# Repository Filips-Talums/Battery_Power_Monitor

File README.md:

# Supply_Power_Monitor

## Overview

Battery_Power_Monitor is an ESP32-based DC inline power monitor designed to measure voltage, current, and power while a DC source powers an external load.

The system is designed to support a wide range of DC input sources from 6 V to 12 V and aims to act as a compact monitoring tool for electronics development and testing.

---

## Project Goals

Through this project I aim to learn:

- PCB design using KiCad
- Circuit testing and calibration
- ESP32 microcontroller development
- Embedded systems programming using C++
- Professional project documentation using GitHub
- Power monitoring and sensor integration

---

## Components Used

- ESP32 Development Board
- INA226 Power Monitoring Sensor
- 128x64 I2C OLED Display
- 6 V buck-boost converter module for powering the ESP32 from a 6–12 V input
- Screw Terminals
- Electrolytic and Ceramic Capacitors
- Fuse Protection

---

## How It Works

An external DC power source between 6 V and 12 V is connected through screw terminals.

The input power is split into two sections:

- A regulated 6 V supply powers the ESP32 and OLED display
- The main power line passes through the INA226 current and voltage sensor before reaching the external load

The INA226 measures:

- Bus Voltage
- Current Draw
- Power Consumption

The ESP32 processes this data and displays the measured values on the OLED screen.

The device is intended to help monitor power usage, diagnose faults, and test small electronics projects safely.

---

## System Diagram

### Power Flow

```text
DC Input (6 V - 12 V)
        │
        ├──→ LM2596S Buck Converter (5 V)
        │          │
        │          └──→ ESP32 ──→ OLED Display
        │                        └──→ Buzzer Warning
        │                        └──→ LED Warning
        └──→ Fuse Protection
                   │
                   └──→ INA226 Power Monitor
                                │
                                └──→ Load Output
```
## Current Status

The breadboard prototype is now working. The ESP32 successfully reads bus voltage and shunt voltage from the INA226 power monitoring sensor and displays voltage, current, and power on the OLED display.

Initial voltage calibration has been completed using a multimeter. The raw INA226 bus voltage reading was found to be consistently higher than the multimeter reading, so a software correction factor was applied.

Current calculation has been implemented using the INA226 shunt voltage and the R100 0.1 Ω shunt resistor. Initial current testing has been carried out using resistor loads and a multimeter. The monitor initially under-read current slightly, so a current correction factor was added in software. Further load testing with higher-current loads is still planned.

* Project requirements defined
* Main components selected
* System block diagram completed
* PlatformIO project created
* INA226 integrated with the ESP32
* OLED display integrated and tested
* Live voltage, current and power measurements displayed
* Voltage readings calibrated against a multimeter
* Current readings tested and calibrated using multiple resistive loads
* Breadboard prototype completed and tested
* Circuit transferred from breadboard to perfboard
* LM2596 buck converter configured to provide a regulated 5 V supply
* Schottky diode and polyfuse protection added
* LED and buzzer fault indicators added
* ESP32 mounted using removable female headers
* Initial perfboard wiring faults identified and repaired
* Perfboard prototype powered and operating successfully
* Breadboard and perfboard software versions organised separately
* Manufacturing process, testing and troubleshooting documented
* Project images added to the documentation

## Project Images

### Top View — Arduino Load at 8.76 V

### Isometric View — Power Monitor and Arduino Load

### Side View of the Device

### Isometric View — Arduino Load at 11.68 V

### Isometric View — Arduino Load at 8.78 V Input

## Next Steps

* Complete extended testing with higher-current loads
* Confirm the 2 A warning system under a controlled load
* Design a custom PCB in KiCad
* Add suitable connectors and component footprints
* Design or manufacture an enclosure
* Perform final accuracy, thermal and reliability testing

## Software

- [Breadboard Prototype V1](software/breadboard-prototype-v1/)

- [Perfboard Prototype V2](software/perfboard-prototype-v2/)

## Project Documentation

- [Design Process](Design_Process.md)
- [Hardware Files](hardware/)
- [Software](software/)
- [Examples](examples/)
- [Learning Notes](docs/learning/)

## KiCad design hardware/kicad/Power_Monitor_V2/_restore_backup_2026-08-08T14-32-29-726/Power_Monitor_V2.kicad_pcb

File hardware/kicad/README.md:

# KiCad Designs

This directory preserves the project's KiCad design history and manufacturing files:

- `Power_Monitor_V1/` contains the first PCB design.
- `Power_Monitor_V2/` contains the version 2 project, its libraries, 3D model, and tracked recovery material.
- The top-level `Power_Monitor_V2.1.kicad_*` files contain the later version 2.1 board project files.
- `PCB_V2_PRINTING/` and `PCB_V2_PRINTING.zip` contain version 2 manufacturing outputs.

Recovery and historical files are intentionally retained. Open the version matching the project stage you want to inspect.

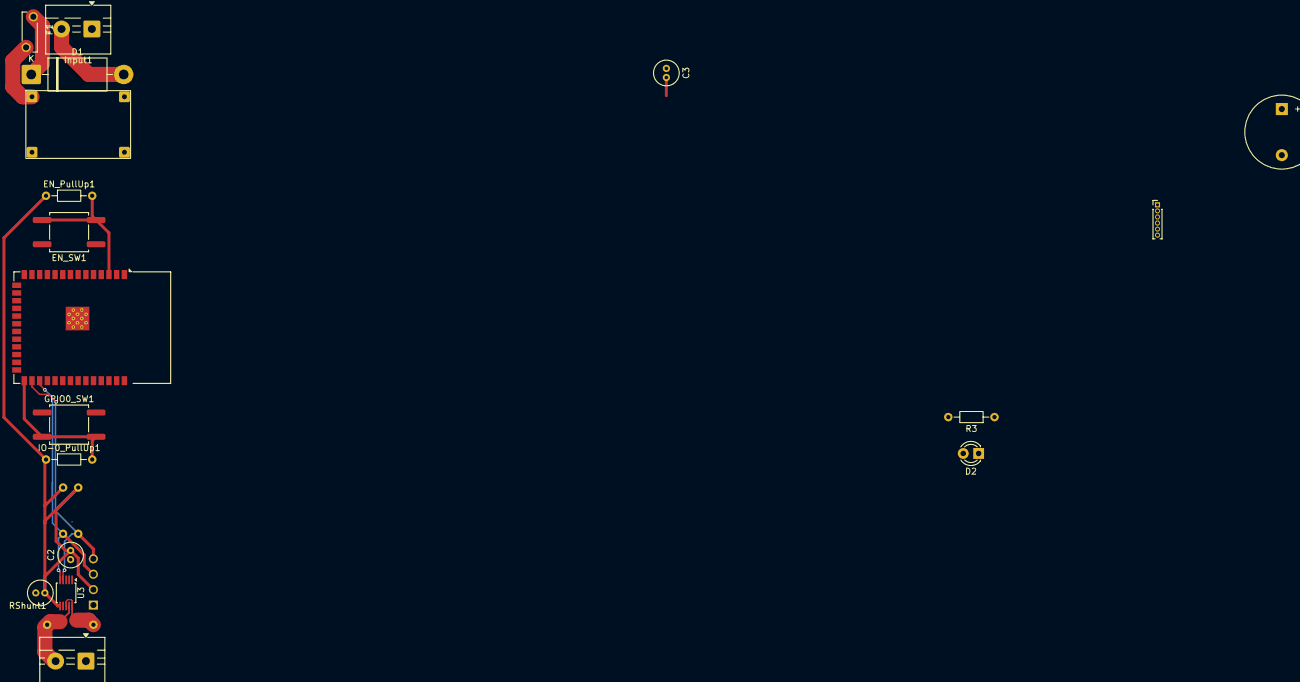
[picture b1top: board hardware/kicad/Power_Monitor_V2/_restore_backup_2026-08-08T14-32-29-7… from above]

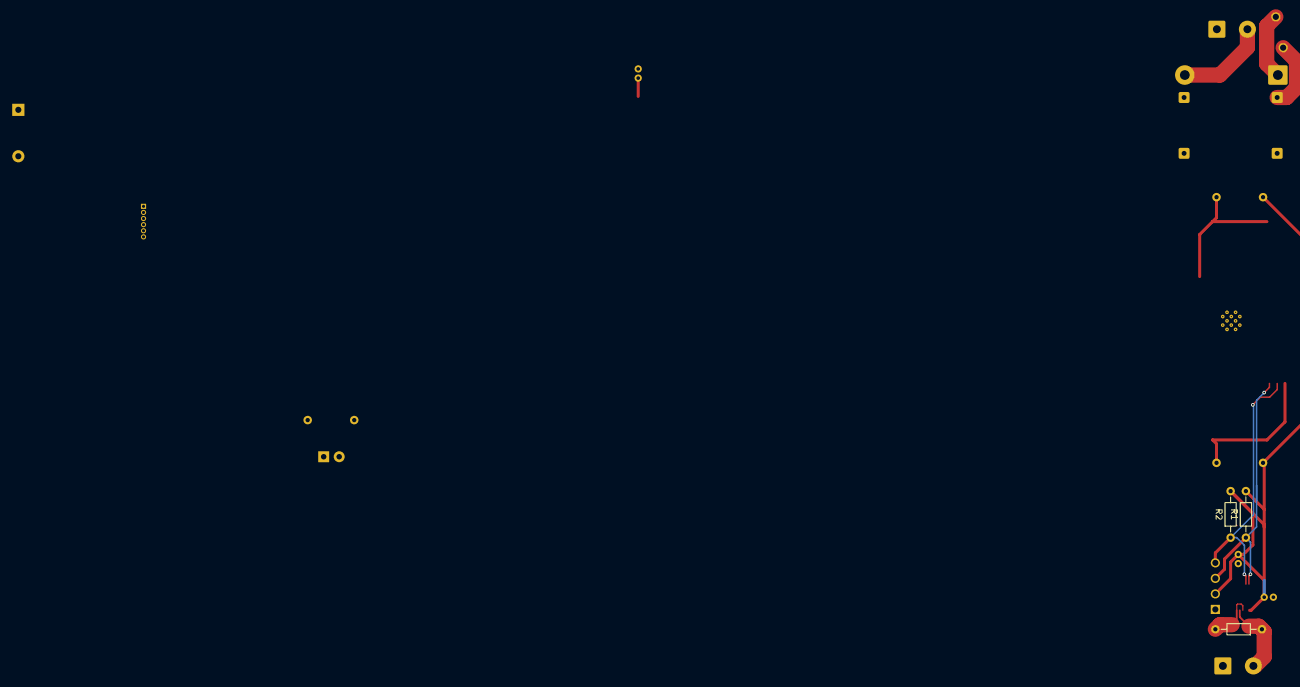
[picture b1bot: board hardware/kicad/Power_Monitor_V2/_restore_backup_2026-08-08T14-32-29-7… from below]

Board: 2 copper layers, 22 parts (3 on the bottom side), 15 nets.

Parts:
BZ1: Buzzer; Buzzer_12x9.5RM7.6
C1, C2, C3: 0.1uf; C_Radial_D4.0mm_H5.0mm_P1.50mm
D1: 1N5822; D_DO-201AD_P15.24mm_Horizontal
D2: LED; LED_D3.0mm
EN_PullUp1: 10k; R_Axial_DIN0204_L3.6mm_D1.6mm_P7.62mm_Horizontal
EN_SW1: SW_Push; SW_Push_1P1T_NO_CK_KSC6xxG
F1: Polyfuse; Polyfuse_2A
GPIO0_SW1: SW_Push; SW_Push_1P1T_NO_CK_KSC6xxG
IO-0_PullUp1: 10k; R_Axial_DIN0204_L3.6mm_D1.6mm_P7.62mm_Horizontal
Input1: Screw_Terminal_01x02; TerminalBlock_MaiXu_MX126-5.0-02P_1x02_P5.00mm
Output1: Screw_Terminal_01x02; TerminalBlock_MaiXu_MX126-5.0-02P_1x02_P5.00mm
R1, R2: 4.7k; R_Axial_DIN0204_L3.6mm_D1.6mm_P7.62mm_Horizontal
R3: 330; R_Axial_DIN0204_L3.6mm_D1.6mm_P7.62mm_Horizontal
RShunt1: 0.03; R_Axial_DIN0204_L3.6mm_D1.6mm_P7.62mm_Horizontal
U1: mini360_module
U2: ESP32-S3-WROOM-1
U3: INA226; TSSOP-10_3x3mm_P0.5mm
U4: DM-OLED096-636; MODULE_DM-OLED096-636_PINS
U5: PinHeader_1x06_P1.00mm_Vertical

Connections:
+3.3V: C1.1, C2.2, C3.2, EN_PullUp1.1, IO-0_PullUp1.1, R1.2, R2.2, U1.3 (Out+), U2.2 (3V3), U3.6 (VS), U4.2 (VCC_IN), U5.6 (3.3V)
+15V: F1.2, RShunt1.2, U1.1 (In+), U3.8 (Vbus), U3.10 (Vin+)
GNDREF: BZ1.2 (-), C1.2, C2.1, C3.1, D2.1 (K), EN_SW1.2, GPIO0_SW1.2, Input1.1, U1.2 (In-), U1.4 (Out-), U2.1 (GND), U2.40 (GND), U2.41 (GND), U3.7 (GND), U4.1 (GND), U5.1 (GND)
unnamed: BZ1.1 (+), U2.16 (IO46)
unnamed: D1.2 (A), Input1.2
unnamed: D1.1 (K), F1.1
unnamed: D2.2 (A), R3.2
unnamed: Output1.2, RShunt1.1, U3.9 (Vin-)
unnamed: EN_PullUp1.2, EN_SW1.1, U2.3 (EN)
unnamed: GPIO0_SW1.1, IO-0_PullUp1.2, U2.27 (IO0)
unnamed: R2.1, U2.28 (IO35), U3.4 (SDA), U4.4 (SDA)
unnamed: R1.1, U2.29 (IO36), U3.5 (SCL), U4.3 (SCL)
unnamed: R3.1, U2.24 (IO47)
unnamed: U2.36 (RXD0), U5.4 (RXD)
unnamed: U2.37 (TXD0), U5.3 (TXD)

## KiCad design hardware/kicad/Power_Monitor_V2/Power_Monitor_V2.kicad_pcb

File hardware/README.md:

# Hardware

- [KiCad](kicad/) contains PCB design sources, earlier board versions, manufacturing outputs, and recovery material.
- [Schematics](schematics/) contains exported circuit diagrams.
- [Datasheets](datasheets/) contains component reference documents used by the project.

All historical design and manufacturing files are retained so that earlier project stages remain reproducible.

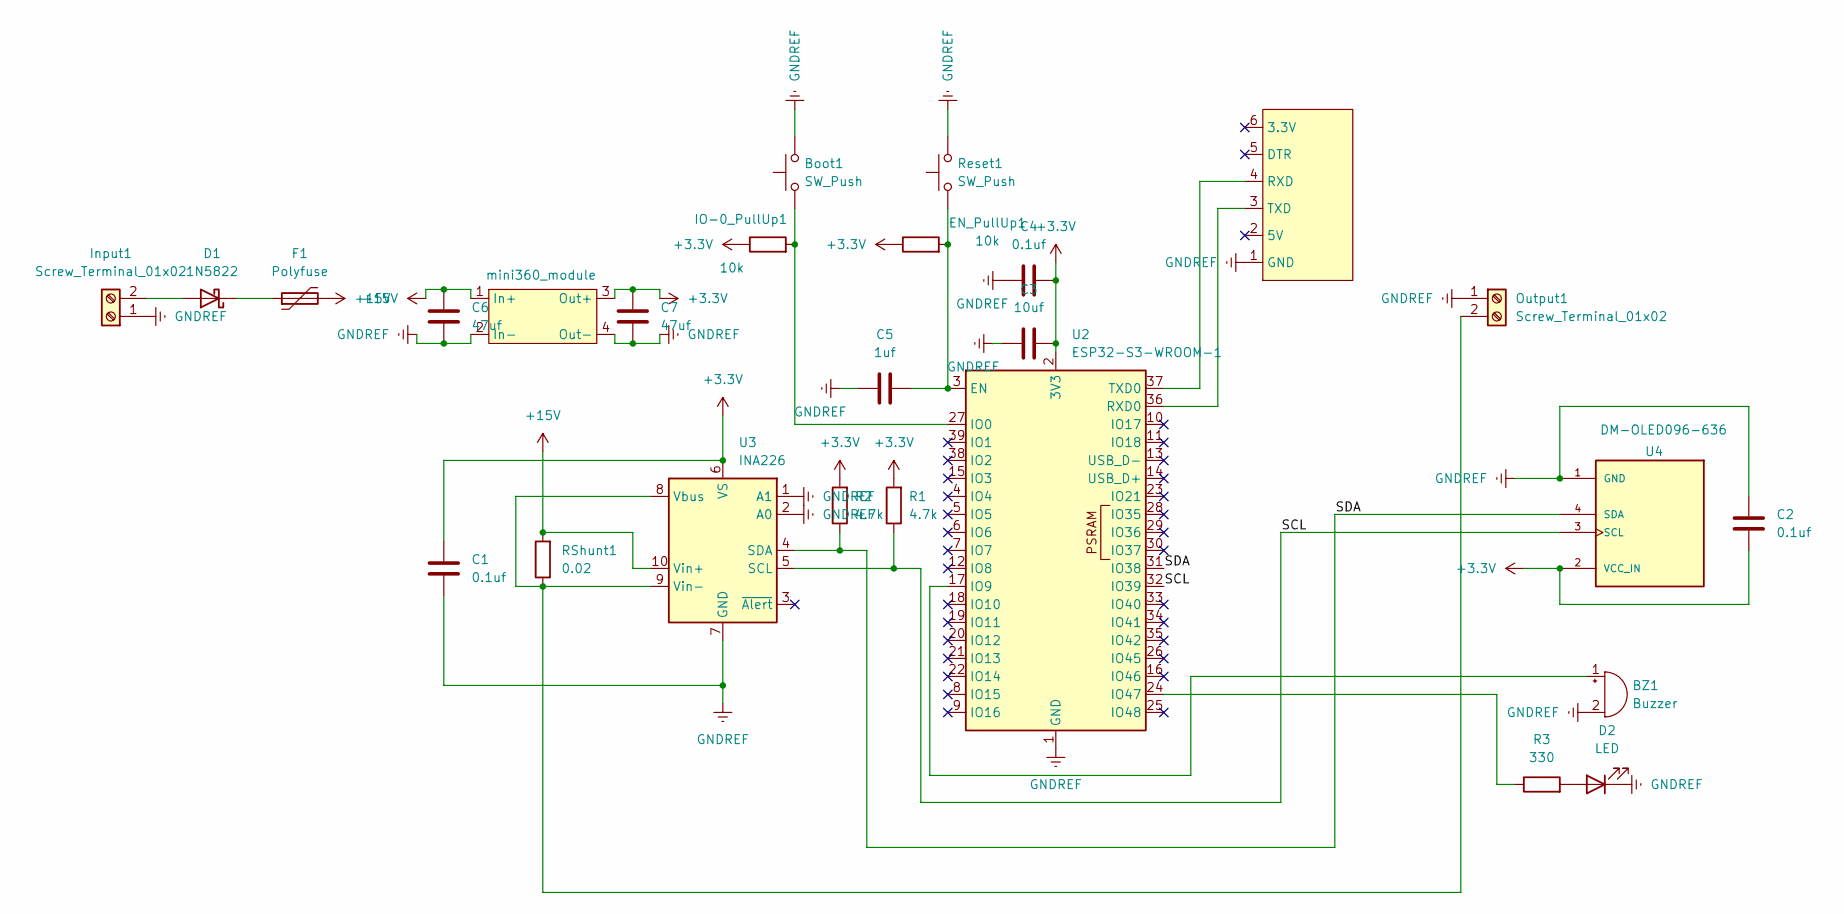
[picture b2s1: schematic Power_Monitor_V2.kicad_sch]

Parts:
BZ1: Buzzer; Buzzer_12x9.5RM7.6
Boot1: SW_Push; SW_Push_1P1T_NO_CK_KSC6xxG
C1, C2, C4: 0.1uf; C_0805_2012Metric_Pad1.18x1.45mm_HandSolder
C3: 10uf; C_0805_2012Metric_Pad1.18x1.45mm_HandSolder
C5: 1uf; C_0805_2012Metric_Pad1.18x1.45mm_HandSolder
C6, C7: 47uf; C_0805_2012Metric_Pad1.18x1.45mm_HandSolder
D1: 1N5822; D_DO-201AD_P15.24mm_Horizontal
D2: LED; C_0805_2012Metric_Pad1.18x1.45mm_HandSolder
EN_PullUp1: 10k; R_0603_1608Metric_Pad0.98x0.95mm_HandSolder
F1: Polyfuse; Polyfuse_Radial_L13mm_W2mm_P4.5mm_D0.8mm
IO-0_PullUp1: 10k; R_0603_1608Metric_Pad0.98x0.95mm_HandSolder
Input1: Screw_Terminal_01x02; TerminalBlock_MaiXu_MX126-5.0-02P_1x02_P5.00mm
Output1: Screw_Terminal_01x02; TerminalBlock_MaiXu_MX126-5.0-02P_1x02_P5.00mm
R1, R2: 4.7k; R_Axial_DIN0204_L3.6mm_D1.6mm_P7.62mm_Horizontal
R3: 330; R_0603_1608Metric
RShunt1: 0.02; R_Axial_DIN0204_L3.6mm_D1.6mm_P7.62mm_Horizontal
Reset1: SW_Push; SW_Push_1P1T_NO_CK_KSC6xxG
U1: mini360_module
U2: ESP32-S3-WROOM-1
U3: INA226; TSSOP-10_3x3mm_P0.5mm
U4: DM-OLED096-636; MODULE_DM-OLED096-636_PINS; PARTREV 2018-09-10
U5: PinHeader_1x06_P2.00mm_Vertical

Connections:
+3.3V: C1.1, C2.2, C3.2, C4.2, C7.1, EN_PullUp1.1, IO-0_PullUp1.1, R1.2, R2.2, U1.3 (Out+), U2.2 (3V3), U3.6 (VS), U4.2 (VCC_IN)
+15V: C6.1, F1.2, RShunt1.2, U1.1 (In+), U3.10 (Vin+)
/SCL: R1.1, U2.32 (IO39), U3.5 (SCL), U4.3 (SCL)
/SDA: R2.1, U2.31 (IO38), U3.4 (SDA), U4.4 (SDA)
GNDREF: BZ1.2 (-), Boot1.2, C1.2, C2.1, C3.1, C4.1, C5.1, C6.2, C7.2, D2.1 (K), Input1.1, Output1.1, Reset1.2, U1.2 (In-), U1.4 (Out-), U2.1 (GND), U2.40 (GND), U2.41 (GND), U3.1 (A1), U3.2 (A0), U3.7 (GND), U4.1 (GND), U5.1 (GND)
unnamed: BZ1.1 (+), U2.17 (IO9)
unnamed: D1.2 (A), Input1.2
unnamed: D1.1 (K), F1.1
unnamed: D2.2 (A), R3.2
unnamed: Output1.2, RShunt1.1, U3.8 (Vbus), U3.9 (Vin-)
unnamed: C5.2, EN_PullUp1.2, Reset1.1, U2.3 (EN)
unnamed: Boot1.1, IO-0_PullUp1.2, U2.27 (IO0)
unnamed: R3.1, U2.24 (IO47)
unnamed: U2.36 (RXD0), U5.3 (TXD)
unnamed: U2.37 (TXD0), U5.4 (RXD)

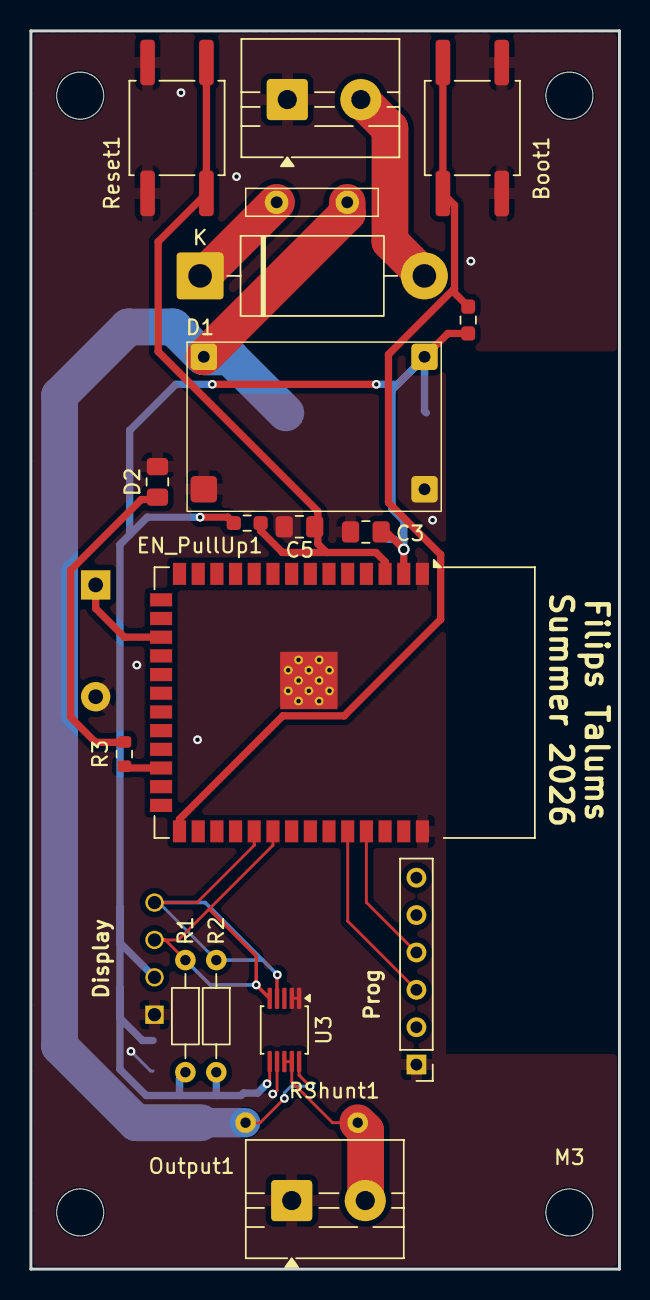
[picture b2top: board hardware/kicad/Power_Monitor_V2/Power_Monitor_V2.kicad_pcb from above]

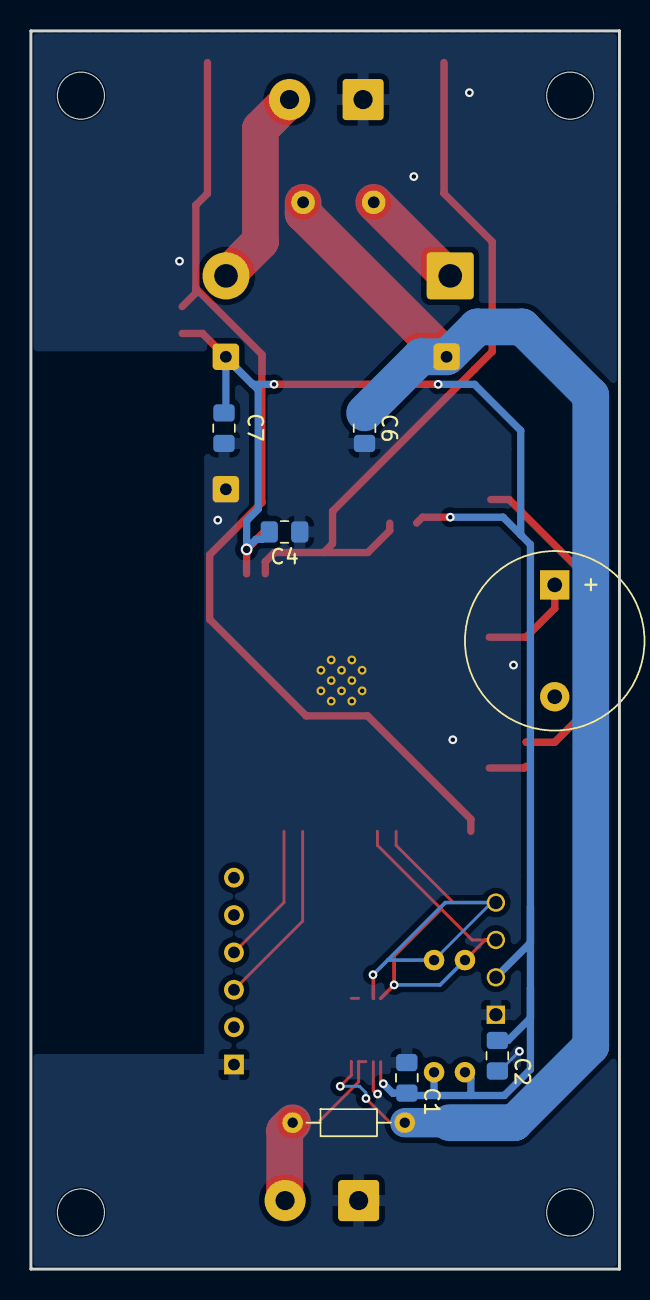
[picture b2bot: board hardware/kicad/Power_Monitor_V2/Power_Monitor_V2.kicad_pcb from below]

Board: 2 copper layers, 40.0 x 84.2 mm, 27 parts (7 on the bottom side), 15 nets.

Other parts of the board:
M3: MountingHole_3.2mm_M3_DIN965

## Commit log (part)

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2026-05-09 Expand README with project details and components
    Added detailed project overview, learning goals, components, and operational explanation.
2026-05-09 Fix formatting and spelling in README.md
    Corrected formatting and spelling errors in the README.
2026-05-09 Add design process documentation for power monitor
    Document the design process for a power monitor project, outlining project aim, problem statement, design requirements, system overview, component selection, circuit design, software design, prototyp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
2026-05-09 Update design requirements and improve clarity
    Revised design requirements for the project, improving clarity and correcting spelling errors.
2026-05-09 Rename Design Process to Design_Process.md
2026-05-14 Rename main.ccp to main.cpp
2026-05-14 Add configuration header for I2C and output pins
2026-05-15 This is temp to test compile
2026-05-15 Create PlatformIO Learning Notes
2026-05-15 Rename PlatformIO Learning Notes to Learning_PlatformIO.md
2026-05-15 Organise repository structure
2026-05-15 Remove macOS system files
2026-05-15 Add system diagram
2026-05-15 Add exported system diagram
2026-05-23 Organise project folders
2026-05-23 Create INA226_Test
2026-05-23 Create OLED_Display_Test
2026-05-23 Rename INA226_Test to ina226_test.md
2026-05-23 Rename buck_convertor.md to buck_convertor_test.md
2026-05-23 Rename OLED_Display_Test to oled_display_test.md
2026-05-30 Add breadboard prototype V1 software
2026-05-30 Update calibrated breadboard prototype software
2026-05-30 Update breadboard prototype software documentation
2026-06-21 Add perfboard software and updated documents
2026-06-21 Update README with project images
2026-06-21 Add perfboard prototype software link
